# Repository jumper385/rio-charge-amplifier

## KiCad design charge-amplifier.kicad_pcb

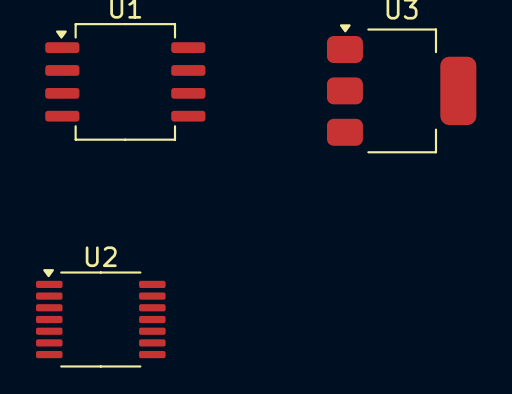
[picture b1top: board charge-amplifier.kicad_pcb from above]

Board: 2 copper layers, 3 parts (0 on the bottom side), 9 nets, no tracks yet.

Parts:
U1: OPA928; SOIC-8_5.3x6.2mm_P1.27mm
U2: TSSOP-14_4.4x5mm_P0.65mm
U3: NCP1117-3.3_SOT223; SOT-223-3_TabPin2

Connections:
GND: U1.4, U2.11, U3.1 (GND)
unnamed: U1.7 (GRD), U1.8 (+)
unnamed: U1.1 (-), U1.2 (GRD)
unnamed: U2.6 (-), U2.7, U2.10 (+)
unnamed: U2.8, U2.9 (-), U2.12 (+)
unnamed: U2.13 (-), U2.14
unnamed: U1.6, U2.3 (+)
unnamed: U2.1, U2.2 (-), U2.5 (+)
VDD: U1.5, U2.4, U3.2 (VO)

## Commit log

2025-07-30 First Commit 🚀
2025-07-30 Update .gitignore to include additional LaTeX output files and temporary files
2025-07-30 Fix junction and wire coordinates in charge amplifier schematic
2025-07-30 Add compliance testing documentation and report template for IEC 61000-4-2
2025-07-31 Refine performance measurement procedures for EUT testing, including baseline data recording and Wasserstein distance comparison.
